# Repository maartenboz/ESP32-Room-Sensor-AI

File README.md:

# ESP32 Room Sensor AI

An open-source ESP32-S3 room sensor and control board designed in KiCad 10. The board measures temperature and relative humidity and provides programmable buttons, potentiometers, LEDs, USB-C power, USB-UART communication and automatic firmware download/reset control.

## Why this project exists

This board was created as an experiment: how far can an AI coding agent go when it is given access to KiCad through an MCP server? The complete engineering workflow was AI-driven—from reading the initial brief and selecting parts to drawing the schematic, assigning footprints, placing and routing the PCB, running checks, producing documentation and publishing this repository. The human supplied the requirements, approved the plan and handled the GitHub login; the board itself was not manually drawn in KiCad by the human.

The experiment used **OpenAI Codex with a GPT-5-based model**, the `KiCad-agentic` MCP server, KiCad 10 CLI/API tooling and Freerouting. See the [AI build log](docs/AI_BUILD_LOG.md) for the short workflow, limitations and measurable run information. The complete [original Dutch prompt](docs/ORIGINAL_PROMPT.md) is preserved with the project.

This is an AI-generated engineering experiment, not proof that the design is production-ready. Automated checks and a plausible layout do not replace review by an experienced hardware engineer or testing of a manufactured prototype.

## Features

- Espressif `ESP32-S3-WROOM-1-N8` with Wi-Fi and Bluetooth LE
- Sensirion `SHT40-AD1B-R2` temperature and humidity sensor on a thermally isolated PCB peninsula
- FTDI `FT231XS-R` USB-to-UART bridge with hardware RX/TX activity LEDs
- USB-C power and programming, USB ESD protection and resettable VBUS fuse
- Automatic ESP32 download/reset circuit plus dedicated BOOT and RESET buttons
- Two active-low user buttons, two 10 kΩ ADC potentiometers and two programmable LEDs
- AP63203 3.3 V synchronous buck supply
- Four-layer, 85 × 55 mm PCB with four M3 mounting holes
- Dedicated ESP32 antenna keepout and continuous inner GND reference plane

## PCB views

| Top | Bottom |
|---|---|
|  |  |

## Project files

- [Schematic PDF](docs/pdf/ESP32-Room-Sensor-Schematic.pdf)
- [Four-page PCB layer PDF](docs/pdf/ESP32-Room-Sensor-PCB.pdf)
- [Bill of materials](bom/KiCad_MCP_Test_BOM.csv)
- [GPIO map](docs/GPIO_MAP.md)
- [Design notes](docs/DESIGN_NOTES.md)
- [Verification record](docs/VERIFICATION.md)
- [AI build log and provenance](docs/AI_BUILD_LOG.md)
- [Original project prompt](docs/ORIGINAL_PROMPT.md)

Open `KiCad_MCP_Test.kicad_pro` with KiCad 10.0.8 or newer. The editable schematic and PCB sources are included; the PDF and PNG files are convenience release artifacts and do not replace the KiCad source.

## Verification status

The schematic ERC currently reports 0 errors and 0 warnings. KiCad-agentic's filtered DRC reports 0 active violations and 0 unconnected items. A fresh native KiCad CLI run that includes the current project rule set reports 323 geometric rule findings and 152 schematic/PCB field-parity findings. The geometric findings are dominated by 0.15 mm routed neck-downs against a 0.20 mm project minimum, clearance/hole rules and connector-edge geometry; the parity findings mainly concern footprint metadata. These findings are documented rather than silently suppressed and must be reviewed against the selected fabricator's rules before manufacturing.

USB differential impedance must be recalculated for the selected fabrication stackup. USB operation, RF/EMC performance and the assembled SHT40 temperature offset require first-article measurement. This repository is an engineering design release, not a certification or production approval.

## License

The creator-controlled hardware design sources and documentation are released under the [CERN Open Hardware Licence Version 2 — Strongly Reciprocal](LICENSE), SPDX identifier `CERN-OHL-S-2.0`. Third-party components, KiCad libraries, manufacturer models and trademarks remain subject to their respective terms.

---

# ESP32-kamersensor AI

Dit is een open-source ESP32-S3-kamersensor en bedieningsprint, ontworpen met KiCad 10. Het bord meet temperatuur en relatieve luchtvochtigheid en bevat programmeerbare knoppen, potentiometers en leds. Voeding, programmeren en seriële communicatie verlopen via USB-C.

## Waarom dit project bestaat

Dit bord is gemaakt als experiment: hoe ver kan een AI-codingagent komen wanneer die via een MCP-server toegang krijgt tot KiCad? De volledige engineeringworkflow werd door AI uitgevoerd—van het lezen van de opdracht en de componentkeuze tot het tekenen van het schema, toewijzen van footprints, plaatsen en routeren van de PCB, uitvoeren van controles, schrijven van documentatie en publiceren van deze repository. De mens leverde de eisen, keurde het plan goed en verzorgde de GitHub-login; het bord is niet handmatig door de mens in KiCad getekend.

Voor het experiment zijn **OpenAI Codex met een GPT-5-gebaseerd model**, de `KiCad-agentic` MCP-server, KiCad 10 CLI/API-tools en Freerouting gebruikt. Zie het [AI-bouwlogboek](docs/AI_BUILD_LOG.md) voor de beknopte werkwijze, beperkingen en meetbare uitvoeringsinformatie. De volledige [oorspronkelijke Nederlandstalige prompt](docs/ORIGINAL_PROMPT.md) is eveneens bewaard.

Dit is een door AI gegenereerd engineeringexperiment, geen bewijs dat het ontwerp productierijp is. Geautomatiseerde controles en een aannemelijke layout vervangen geen beoordeling door een ervaren hardware-engineer of tests op een geproduceerd prototype.

## Functies

- Espressif `ESP32-S3-WROOM-1-N8` met wifi en Bluetooth LE
- Sensirion `SHT40-AD1B-R2` op een thermisch geïsoleerd PCB-schiereiland
- FTDI `FT231XS-R` USB-UART-bridge met echte hardwarematige RX/TX-indicatie
- USB-C, USB-ESD-beveiliging en een resetbare VBUS-zekering
- Automatische download/resetbesturing plus afzonderlijke BOOT- en RESET-knoppen
- Twee active-low gebruikersknoppen, twee 10 kΩ ADC-potmeters en twee programmeerbare leds
- AP63203 synchrone 3,3V-buckregelaar
- Vierlaagse PCB van 85 × 55 mm met vier M3-montagegaten
- ESP32-antennekeepout en een ononderbroken interne GND-referentielaag

## PCB-aanzichten

| Bovenkant | Onderkant |
|---|---|
|  |  |

## Projectbestanden

- [Schema als PDF](docs/pdf/ESP32-Room-Sensor-Schematic.pdf)
- [Vierpagina-PDF van de PCB-lagen](docs/pdf/ESP32-Room-Sensor-PCB.pdf)
- [Componentenlijst](bom/KiCad_MCP_Test_BOM.csv)
- [GPIO-toewijzing](docs/GPIO_MAP.md)
- [Ontwerpnotities](docs/DESIGN_NOTES.md)
- [Verificatierapport](docs/VERIFICATION.md)
- [AI-bouwlogboek en herkomst](docs/AI_BUILD_LOG.md)
- [Oorspronkelijke projectprompt](docs/ORIGINAL_PROMPT.md)

Open `KiCad_MCP_Test.kicad_pro` met KiCad 10.0.8 of nieuwer. De bewerkbare schema- en PCB-bronnen zijn opgenomen; PDF- en PNG-bestanden zijn aanvullende release-artifacts.

## Verificatiestatus

De ERC van het schema rapporteert momenteel 0 fouten en 0 waarschuwingen. De gefilterde KiCad-agentic DRC rapporteert 0 actieve overtredingen en 0 niet-aangesloten items. Een nieuwe native KiCad CLI-run met de huidige projectregels rapporteert 323 geometrische regelmeldingen en 152 schema/PCB-veldpariteitsmeldingen. De geometrische meldingen bestaan hoofdzakelijk uit lokale 0,15mm-neckdowns tegenover een projectminimum van 0,20 mm, clearance-/gatregels en connectorgeometrie; de pariteitsmeldingen gaan vooral over footprintmetadata. Deze punten zijn bewust gedocumenteerd en moeten vóór fabricage aan de regels van de gekozen fabrikant worden getoetst.

De USB-impedantie moet opnieuw worden berekend voor de gekozen productiestackup. USB-functionaliteit, RF/EMC-prestaties en de temperatuur-offset van de gemonteerde SHT40 moeten op een eerste prototype worden gemeten. Deze repository is een engineering-release en geen certificering of productiegoedkeuring.

## Licentie

De door de ontwerper beheerde hardwarebronnen en documentatie vallen onder de [CERN Open Hardware Licence Version 2 — Strongly Reciprocal](LICENSE), SPDX-identificatie `CERN-OHL-S-2.0`. Componenten, KiCad-libraries, fabrikantmodellen en handelsmerken van derden behouden hun eigen voorwaarden.

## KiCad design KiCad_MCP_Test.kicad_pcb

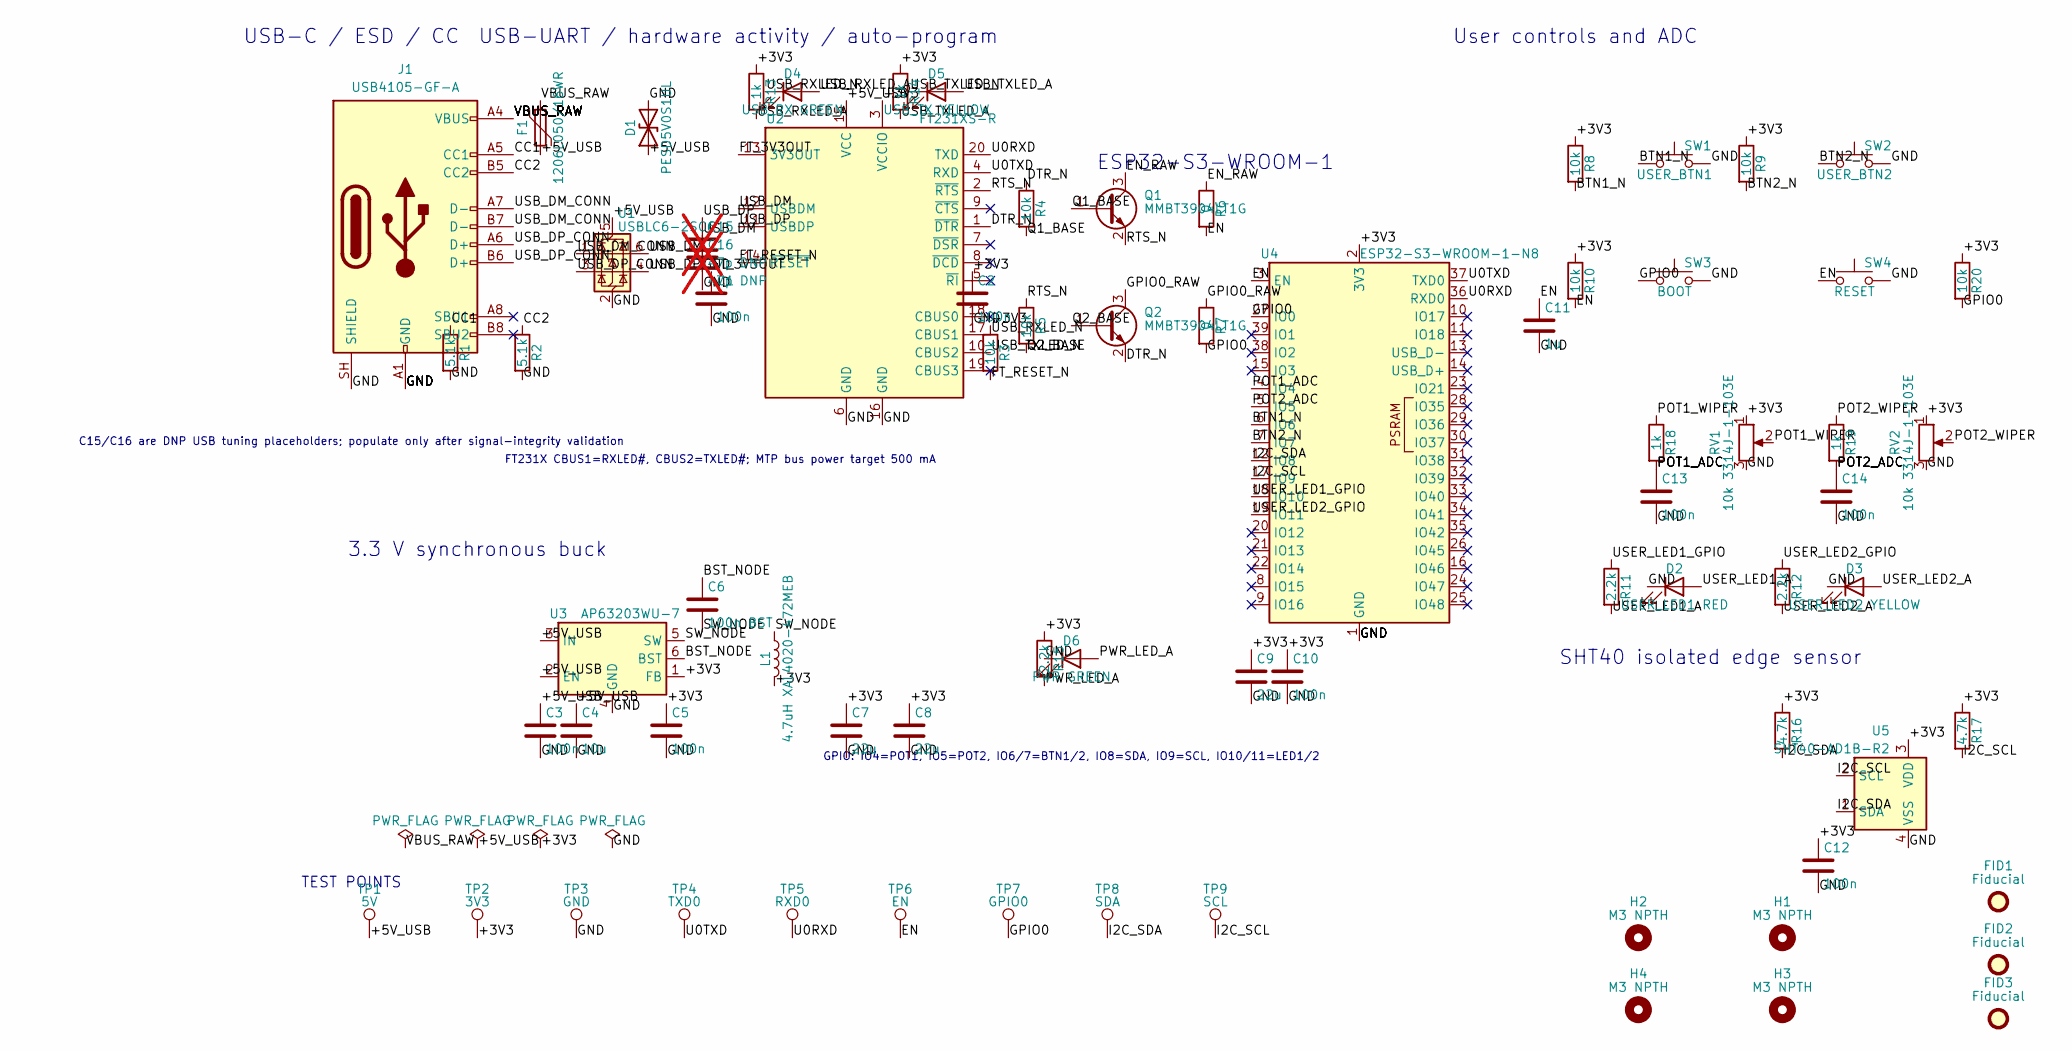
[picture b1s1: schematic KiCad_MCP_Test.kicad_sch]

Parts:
C1, C2, C3, C5, C10, C12, C13, C14: 100n; C_0603_1608Metric; Manufacturer Part Number CC0603KRX7R9BB104
C4: 10u; C_0805_2012Metric; Manufacturer Part Number CC0805MKX5R5BB106
C6: 100n BST; C_0603_1608Metric; Manufacturer Part Number CC0603KRX7R9BB104
C7, C8, C9: 22u; C_0805_2012Metric; Manufacturer Part Number GRM21BR61A226ME44L
C11: 1u; C_0603_1608Metric; Manufacturer Part Number CC0603KRX7R7BB105
C15, C16: 47p DNP; C_0603_1608Metric; Manufacturer Part Number CC0603JRNPO9BN470; not fitted
D1: PESD5V0S1UL; D_SOD-882; Manufacturer Part Number PESD5V0S1UL,315
D2: USER_LED1 RED; LED_0603_1608Metric; Manufacturer Part Number APT1608LSECK
D3: USER_LED2 YELLOW; LED_0603_1608Metric; Manufacturer Part Number APT1608SYCK
D4: USB_RX GREEN; LED_0603_1608Metric; Manufacturer Part Number APT1608SGC
D5: USB_TX YELLOW; LED_0603_1608Metric; Manufacturer Part Number APT1608SYCK
D6: PWR GREEN; LED_0603_1608Metric; Manufacturer Part Number APT1608SGC
F1: 1206L050/16WR; Fuse_1206_3216Metric; Manufacturer Part Number 1206L050/16WR
FID1, FID2, FID3: Fiducial; Fiducial_1mm_Mask2mm
H1, H2, H3, H4: M3 NPTH; MountingHole_3.2mm_M3
J1: USB4105-GF-A; USB_C_Receptacle_GCT_USB4105-xx-A_16P_TopMnt_Horizontal; Manufacturer Part Number USB4105-GF-A
L1: 4.7uH XAL4020-472MEB; L_Coilcraft_XAL4020-XXX; Manufacturer Part Number XAL4020-472MEB
Q1, Q2: MMBT3904LT1G; SOT-23; Manufacturer Part Number MMBT3904LT1G
R1, R2: 5.1k; R_0603_1608Metric; Manufacturer Part Number RC0603FR-075K1L
R3, R4, R5, R8, R9, R10, R20: 10k; R_0603_1608Metric; Manufacturer Part Number RC0603FR-0710KL
R6, R7: 0; R_0603_1608Metric; Manufacturer Part Number RC0603JR-070RL
R11, R12, R15: 2.2k; R_0603_1608Metric; Manufacturer Part Number RC0603FR-072K2L
R13, R14, R18, R19: 1k; R_0603_1608Metric; Manufacturer Part Number RC0603FR-071KL
R16, R17: 4.7k; R_0603_1608Metric; Manufacturer Part Number RC0603FR-074K7L
RV1, RV2: 10k 3314J-1-103E; Potentiometer_Bourns_3314J_Vertical; Manufacturer Part Number 3314J-1-103E
SW1: USER_BTN1; SW_Tactile_SPST_NO_Straight_CK_PTS636Sx25SMTRLFS; Manufacturer Part Number PTS636 SK25 SMTR LFS
SW2: USER_BTN2; SW_Tactile_SPST_NO_Straight_CK_PTS636Sx25SMTRLFS; Manufacturer Part Number PTS636 SK25 SMTR LFS
SW3: BOOT; SW_Tactile_SPST_NO_Straight_CK_PTS636Sx25SMTRLFS; Manufacturer Part Number PTS636 SK25 SMTR LFS
SW4: RESET; SW_Tactile_SPST_NO_Straight_CK_PTS636Sx25SMTRLFS; Manufacturer Part Number PTS636 SK25 SMTR LFS
TP1: 5V; TestPoint_Pad_D1.0mm; Manufacturer Part Number 5015
TP2: 3V3; TestPoint_Pad_D1.0mm; Manufacturer Part Number 5015
TP3: GND; TestPoint_Pad_D1.0mm; Manufacturer Part Number 5015
TP4: TXD0; TestPoint_Pad_D1.0mm; Manufacturer Part Number 5015
TP5: RXD0; TestPoint_Pad_D1.0mm; Manufacturer Part Number 5015
TP6: EN; TestPoint_Pad_D1.0mm; Manufacturer Part Number 5015
TP7: GPIO0; TestPoint_Pad_D1.0mm; Manufacturer Part Number 5015
TP8: SDA; TestPoint_Pad_D1.0mm; Manufacturer Part Number 5015
TP9: SCL; TestPoint_Pad_D1.0mm; Manufacturer Part Number 5015
U1: USBLC6-2SC6; SOT-23-6; Manufacturer Part Number USBLC6-2SC6
U2: FT231XS-R; SSOP-20_3.9x8.7mm_P0.635mm; Manufacturer Part Number FT231XS-R
U3: AP63203WU-7; TSOT-23-6; Manufacturer Part Number AP63203WU-7
U4: ESP32-S3-WROOM-1-N8; ESP32-S3-WROOM-1; Manufacturer Part Number ESP32-S3-WROOM-1-N8
U5: SHT40-AD1B-R2; Sensirion_DFN-4_1.5x1.5mm_P0.8mm_SHT4x_NoCentralPad; Manufacturer Part Number SHT40-AD1B-R2

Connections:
/+3V3: C2.1, C5.1, C7.1, C8.1, C9.1, C10.1, C12.1, L1.2, R3.1, R8.1, R9.1, R10.1, R13.1, R14.1, R15.1, R16.1, R17.1, R20.1, RV1.1, RV2.1, TP2.1, U2.3 (VCCIO), U3.1 (FB), U4.2 (3V3), U5.3 (VDD)
/+5V_USB: C3.1, C4.1, D1.1 (A1), F1.2, TP1.1, U1.5 (VBUS), U2.15 (VCC), U3.2 (EN), U3.3 (IN)
/BST_NODE: C6.1, U3.6 (BST)
/BTN1_N: R8.2, SW1.1, U4.6 (IO6)
/BTN2_N: R9.2, SW2.1, U4.7 (IO7)
/CC1: J1.A5 (CC1), R1.1
/CC2: J1.B5 (CC2), R2.1
/DTR_N: Q2.2 (E), R4.1, U2.1 (~DTR)
/EN: C11.1, R6.2, R10.2, SW4.1, TP6.1, U4.3 (EN)
/EN_RAW: Q1.3 (C), R6.1
/FT_3V3OUT: C1.1, U2.13 (3V3OUT)
/FT_RESET_N: R3.2, U2.14 (~RESET)
/GND: C1.2, C2.2, C3.2, C4.2, C5.2, C7.2, C8.2, C9.2, C10.2, C11.2, C12.2, C13.2, C14.2, C15.2, C16.2, D1.2 (A2), D2.1 (K), D3.1 (K), D6.1 (K), J1.A1 (GND), J1.A12 (GND), J1.B1 (GND), J1.B12 (GND), J1.SH (SHIELD), R1.2, R2.2, RV1.3, RV2.3, SW1.2, SW2.2, SW3.2, SW4.2, TP3.1, U1.2 (GND), U2.6 (GND), U2.16 (GND), U3.4 (GND), U4.1 (GND), U4.40 (GND), U4.41 (GND), U5.4 (VSS)
/GPIO0: R7.2, R20.2, SW3.1, TP7.1, U4.27 (IO0)
/GPIO0_RAW: Q2.3 (C), R7.1
/I2C_SCL: R17.2, TP9.1, U4.17 (IO9), U5.2 (SCL)
/I2C_SDA: R16.2, TP8.1, U4.12 (IO8), U5.1 (SDA)
/POT1_ADC: C13.1, R18.2, U4.4 (IO4)
/POT1_WIPER: R18.1, RV1.2
/POT2_ADC: C14.1, R19.2, U4.5 (IO5)
/POT2_WIPER: R19.1, RV2.2
/PWR_LED_A: D6.2 (A), R15.2
/Q1_BASE: Q1.1 (B), R4.2
/Q2_BASE: Q2.1 (B), R5.2
/RTS_N: Q1.2 (E), R5.1, U2.2 (~RTS)
/SW_NODE: C6.2, L1.1, U3.5 (SW)
/U0RXD: TP5.1, U2.20 (TXD), U4.36 (RXD0)
/U0TXD: TP4.1, U2.4 (RXD), U4.37 (TXD0)
/USB_DM: C16.1, U1.6 (I/O1), U2.12 (USBDM)
/USB_DM_CONN: J1.A7 (D-), J1.B7 (D-), U1.1 (I/O1)
/USB_DP: C15.1, U1.4 (I/O2), U2.11 (USBDP)
/USB_DP_CONN: J1.A6 (D+), J1.B6 (D+), U1.3 (I/O2)
/USB_RXLED_A: D4.2 (A), R13.2
/USB_RXLED_N: D4.1 (K), U2.17 (CBUS1)
/USB_TXLED_A: D5.2 (A), R14.2
/USB_TXLED_N: D5.1 (K), U2.10 (CBUS2)
/USER_LED1_A: D2.2 (A), R11.2
/USER_LED1_GPIO: R11.1, U4.18 (IO10)
/USER_LED2_A: D3.2 (A), R12.2
/USER_LED2_GPIO: R12.1, U4.19 (IO11)
/VBUS_RAW: F1.1, J1.A4 (VBUS), J1.A9 (VBUS), J1.B4 (VBUS), J1.B9 (VBUS)

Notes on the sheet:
USB-C / ESD / CC
USB-UART / hardware activity / auto-program
3.3 V synchronous buck
ESP32-S3-WROOM-1
User controls and ADC
SHT40 isolated edge sensor
TEST POINTS
GPIO: IO4=POT1, IO5=POT2, IO6/7=BTN1/2, IO8=SDA, IO9=SCL, IO10/11=LED1/2
FT231X CBUS1=RXLED#, CBUS2=TXLED#; MTP bus power target 500 mA
C15/C16 are DNP USB tuning placeholders; populate only after signal-integrity validation

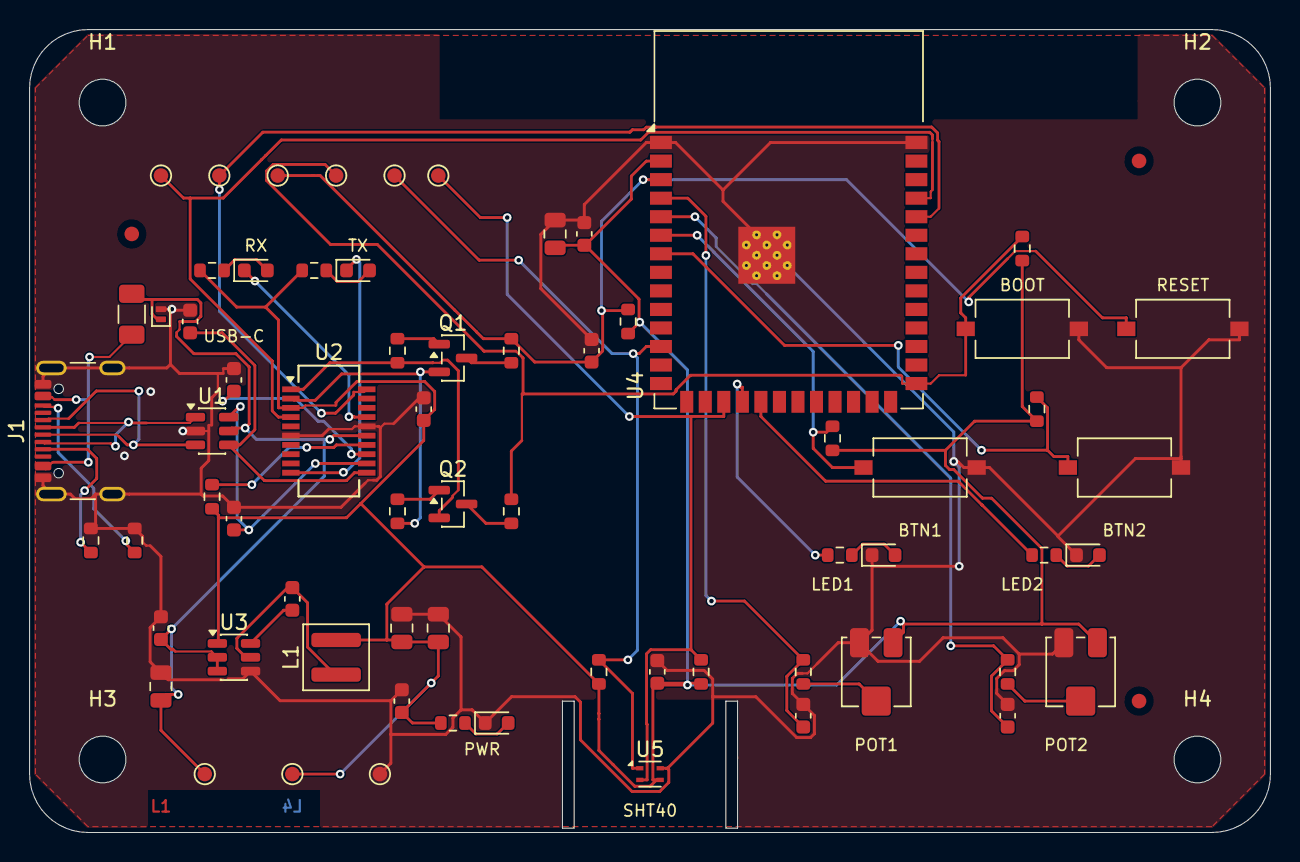
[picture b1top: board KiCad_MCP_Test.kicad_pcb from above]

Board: 4 copper layers, 85.0 x 55.0 mm, 74 parts (0 on the bottom side), 41 nets.

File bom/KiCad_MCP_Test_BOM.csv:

"References","Value","Footprint","Manufacturer","MPN","Datasheet","Description","Quantity"
"C1-C3,C5,C10,C12-C14","100n","Capacitor_SMD:C_0603_1608Metric","Yageo","CC0603KRX7R9BB104","https://www.yageo.com/upload/media/product/productsearch/dat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","","8"
"C4","10u","Capacitor_SMD:C_0805_2012Metric","Yageo","CC0805MKX5R5BB106","https://www.yageo.com/upload/media/product/productsearch/dat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","","1"
"C6","100n BST","Capacitor_SMD:C_0603_1608Metric","Yageo","CC0603KRX7R9BB104","https://www.yageo.com/upload/media/product/productsearch/dat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","","1"
"C7-C9","22u","Capacitor_SMD:C_0805_2012Metric","Murata","GRM21BR61A226ME44L","https://search.murata.co.jp/Ceramy/image/img/A01X/G101/ENG/G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","","3"
"C11","1u","Capacitor_SMD:C_0603_1608Metric","Yageo","CC0603KRX7R7BB105","https://www.yageo.com/upload/media/product/productsearch/dat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","","1"
"D1","PESD5V0S1UL","Diode_SMD:D_SOD-882","Nexperia","PESD5V0S1UL,315","https://assets.nexperia.com/documents/data-sheet/PESD5V0S1UL.pdf","","1"
"D2","USER_LED1 RED","LED_SMD:LED_0603_1608Metric","Kingbright","APT1608LSECK","https://www.kingbrightusa.com/images/catalog/SPEC/APT1608LSECK.pdf","","1"
"D3","USER_LED2 YELLOW","LED_SMD:LED_0603_1608Metric","Kingbright","APT1608SYCK","https://www.kingbrightusa.com/images/catalog/SPEC/APT1608SYCK.pdf","","1"
"D4","USB_RX GREEN","LED_SMD:LED_0603_1608Metric","Kingbright","APT1608SGC","https://www.kingbrightusa.com/images/catalog/SPEC/APT1608SGC.pdf","","1"
"D5","USB_TX YELLOW","LED_SMD:LED_0603_1608Metric","Kingbright","APT1608SYCK","https://www.kingbrightusa.com/images/catalog/SPEC/APT1608SYCK.pdf","","1"
"D6","PWR GREEN","LED_SMD:LED_0603_1608Metric","Kingbright","APT1608SGC","https://www.kingbrightusa.com/images/catalog/SPEC/APT1608SGC.pdf","","1"
"F1","1206L050/16WR","Fuse:Fuse_1206_3216Metric","Littelfuse","1206L050/16WR","https://www.littelfuse.com/media?resourcetype=datasheets&ite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","","1"
"J1","USB4105-GF-A","Connector_USB:USB_C_Receptacle_GCT_USB4105-xx-A_16P_TopMnt_Horizontal","GCT","USB4105-GF-A","https://gct.co/connector/usb4105","","1"
"L1","4.7uH XAL4020-472MEB","Inductor_SMD:L_Coilcraft_XAL4020-XXX","Coilcraft","XAL4020-472MEB","https://www.coilcraft.com/getmedia/78a676e0-1f2d-4e32-b142-5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","","1"
"Q1,Q2","MMBT3904LT1G","Package_TO_SOT_SMD:SOT-23","onsemi","MMBT3904LT1G","https://www.onsemi.com/pdf/datasheet/mmbt3904lt1-d.pdf","","2"
"R1,R2","5.1k","Resistor_SMD:R_0603_1608Metric","Yageo","RC0603FR-075K1L","https://www.yageo.com/upload/media/product/productsearch/dat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","","2"
"R3-R5,R8-R10,R20","10k","Resistor_SMD:R_0603_1608Metric","Yageo","RC0603FR-0710KL","https://www.yageo.com/upload/media/product/productsearch/dat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","","7"
"R6,R7","0","Resistor_SMD:R_0603_1608Metric","Yageo","RC0603JR-070RL","https://www.yageo.com/upload/media/product/productsearch/dat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","","2"
"R11,R12,R15","2.2k","Resistor_SMD:R_0603_1608Metric","Yageo","RC0603FR-072K2L","https://www.yageo.com/upload/media/product/productsearch/dat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","","3"
"R13,R14,R18,R19","1k","Resistor_SMD:R_0603_1608Metric","Yageo","RC0603FR-071KL","https://www.yageo.com/upload/media/product/productsearch/dat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","","4"
"R16,R17","4.7k","Resistor_SMD:R_0603_1608Metric","Yageo","RC0603FR-074K7L","https://www.yageo.com/upload/media/product/productsearch/dat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","","2"
"RV1,RV2","10k 3314J-1-103E","Potentiometer_SMD:Potentiometer_Bourns_3314J_Vertical","Bourns","3314J-1-103E","https://www.bourns.com/docs/product-datasheets/3314.pdf","","2"
"SW1","USER_BTN1","Button_Switch_SMD:SW_Tactile_SPST_NO_Straight_CK_PTS636Sx25SMTRLFS","C&K","PTS636 SK25 SMTR LFS","https://www.ckswitches.com/media/1479/pts636.pdf","","1"
"SW2","USER_BTN2","Button_Switch_SMD:SW_Tactile_SPST_NO_Straight_CK_PTS636Sx25SMTRLFS","C&K","PTS636 SK25 SMTR LFS","https://www.ckswitches.com/media/1479/pts636.pdf","","1"
"SW3","BOOT","Button_Switch_SMD:SW_Tactile_SPST_NO_Straight_CK_PTS636Sx25SMTRLFS","C&K","PTS636 SK25 SMTR LFS","https://www.ckswitches.com/media/1479/pts636.pdf","","1"
"SW4","RESET","Button_Switch_SMD:SW_Tactile_SPST_NO_Straight_CK_PTS636Sx25SMTRLFS","C&K","PTS636 SK25 SMTR LFS","https://www.ckswitches.com/media/1479/pts636.pdf","","1"
"TP1","5V","TestPoint:TestPoint_Pad_D1.0mm","Keystone Electronics","5015","","","1"
"TP2","3V3","TestPoint:TestPoint_Pad_D1.0mm","Keystone Electronics","5015","","","1"
"TP3","GND","TestPoint:TestPoint_Pad_D1.0mm","Keystone Electronics","5015","","","1"
"TP4","TXD0","TestPoint:TestPoint_Pad_D1.0mm","Keystone Electronics","5015","","","1"
"TP5","RXD0","TestPoint:TestPoint_Pad_D1.0mm","Keystone Electronics","5015","","","1"
"TP6","EN","TestPoint:TestPoint_Pad_D1.0mm","Keystone Electronics","5015","","","1"
"TP7","GPIO0","TestPoint:TestPoint_Pad_D1.0mm","Keystone Electronics","5015","","","1"
"TP8","SDA","TestPoint:TestPoint_Pad_D1.0mm","Keystone Electronics","5015","","","1"
"TP9","SCL","TestPoint:TestPoint_Pad_D1.0mm","Keystone Electronics","5015","","","1"
"U1","USBLC6-2SC6","Package_TO_SOT_SMD:SOT-23-6","STMicroelectronics","USBLC6-2SC6","https://www.st.com/resource/en/datasheet/usblc6-2.pdf","","1"
"U2","FT231XS-R","Package_SO:SSOP-20_3.9x8.7mm_P0.635mm","FTDI","FT231XS-R","https://ftdichip.com/wp-content/uploads/2021/10/DS_FT231X.pdf","","1"
"U3","AP63203WU-7","Package_TO_SOT_SMD:TSOT-23-6","Diodes Incorporated","AP63203WU-7","https://www.diodes.com/datasheet/download/AP63200-AP63201-AP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","","1"
"U4","ESP32-S3-WROOM-1-N8","RF_Module:ESP32-S3-WROOM-1","Espressif Systems","ESP32-S3-WROOM-1-N8","https://documentation.espressif.com/esp32-s3-wroom-1_wroom-1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","","1"
"U5","SHT40-AD1B-R2","Sensor_Humidity:Sensirion_DFN-4_1.5x1.5mm_P0.8mm_SHT4x_NoCentralPad","Sensirion","SHT40-AD1B-R2","https://sensirion.com/media/documents/33FD6951/67EB9032/HT_D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","","1"
